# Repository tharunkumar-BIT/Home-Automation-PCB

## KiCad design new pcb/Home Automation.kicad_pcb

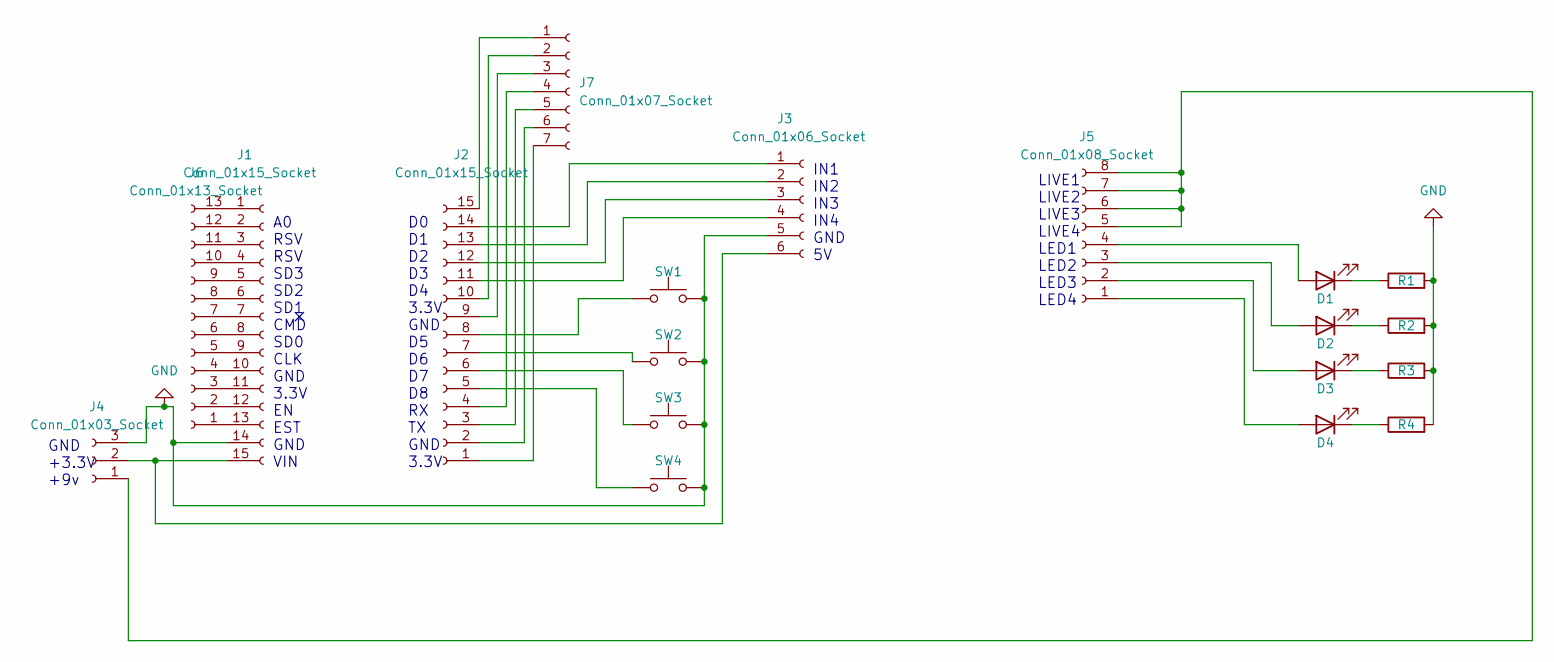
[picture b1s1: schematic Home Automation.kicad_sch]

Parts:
D1, D2, D3, D4: LED; LED_D10.0mm
J1, J2: Conn_01x15_Socket; PinSocket_1x15_P2.54mm_Vertical
J3: Conn_01x06_Socket; PinSocket_1x06_P2.54mm_Vertical
J4: Conn_01x03_Socket; PinSocket_1x03_P2.54mm_Vertical
J5: Conn_01x08_Socket; PinSocket_1x08_P2.54mm_Vertical
J6: Conn_01x13_Socket; PinSocket_1x13_P2.54mm_Vertical
J7: Conn_01x07_Socket; PinSocket_1x07_P2.54mm_Vertical
R1, R2, R3, R4: R; R_Axial_DIN0204_L3.6mm_D1.6mm_P7.62mm_Horizontal
SW1, SW2, SW3, SW4: SW_Push; SW_PUSH_6mm

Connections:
GND: J1.14, J3.5, J4.3, R1.2, R2.2, R3.2, R4.2, SW1.2, SW2.2, SW3.2, SW4.2
unnamed: D1.2 (A), J5.4
unnamed: D1.1 (K), R1.1
unnamed: D2.2 (A), J5.3
unnamed: D2.1 (K), R2.1
unnamed: D3.2 (A), J5.2
unnamed: D3.1 (K), R3.1
unnamed: D4.2 (A), J5.1
unnamed: D4.1 (K), R4.1
unnamed: J1.1, J6.13
unnamed: J1.2, J6.12
unnamed: J1.3, J6.11
unnamed: J1.4, J6.10
unnamed: J1.5, J6.9
unnamed: J1.6, J6.8
unnamed: J1.7, J6.7
unnamed: J1.8, J6.6
unnamed: J1.9, J6.5
unnamed: J1.10, J6.4
unnamed: J1.11, J6.3
unnamed: J1.12, J6.2
unnamed: J1.13, J6.1
unnamed: J1.15, J3.6, J4.2
unnamed: J2.1, J7.7
unnamed: J2.2, J7.6
unnamed: J2.3, J7.5
unnamed: J2.4, J7.4
unnamed: J2.5, SW4.1
unnamed: J2.6, SW3.1
unnamed: J2.7, SW2.1
unnamed: J2.8, SW1.1
unnamed: J2.9, J7.3
unnamed: J2.10, J7.2
unnamed: J2.11, J3.4
unnamed: J2.12, J3.3
unnamed: J2.13, J3.2
unnamed: J2.14, J3.1
unnamed: J2.15, J7.1
unnamed: J4.1, J5.5, J5.6, J5.7, J5.8

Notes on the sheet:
D0 D1 D2 D3 D4 3.3V GND D5 D6 D7 D8 RX TX GND 3.3V
GND +3.3V +9v
IN1 IN2 IN3 IN4 GND 5V
A0 RSV RSV SD3 SD2 SD1 CMD SD0 CLK GND 3.3V EN EST GND VIN
LIVE1 LIVE2 LIVE3 LIVE4 LED1 LED2 LED3 LED4

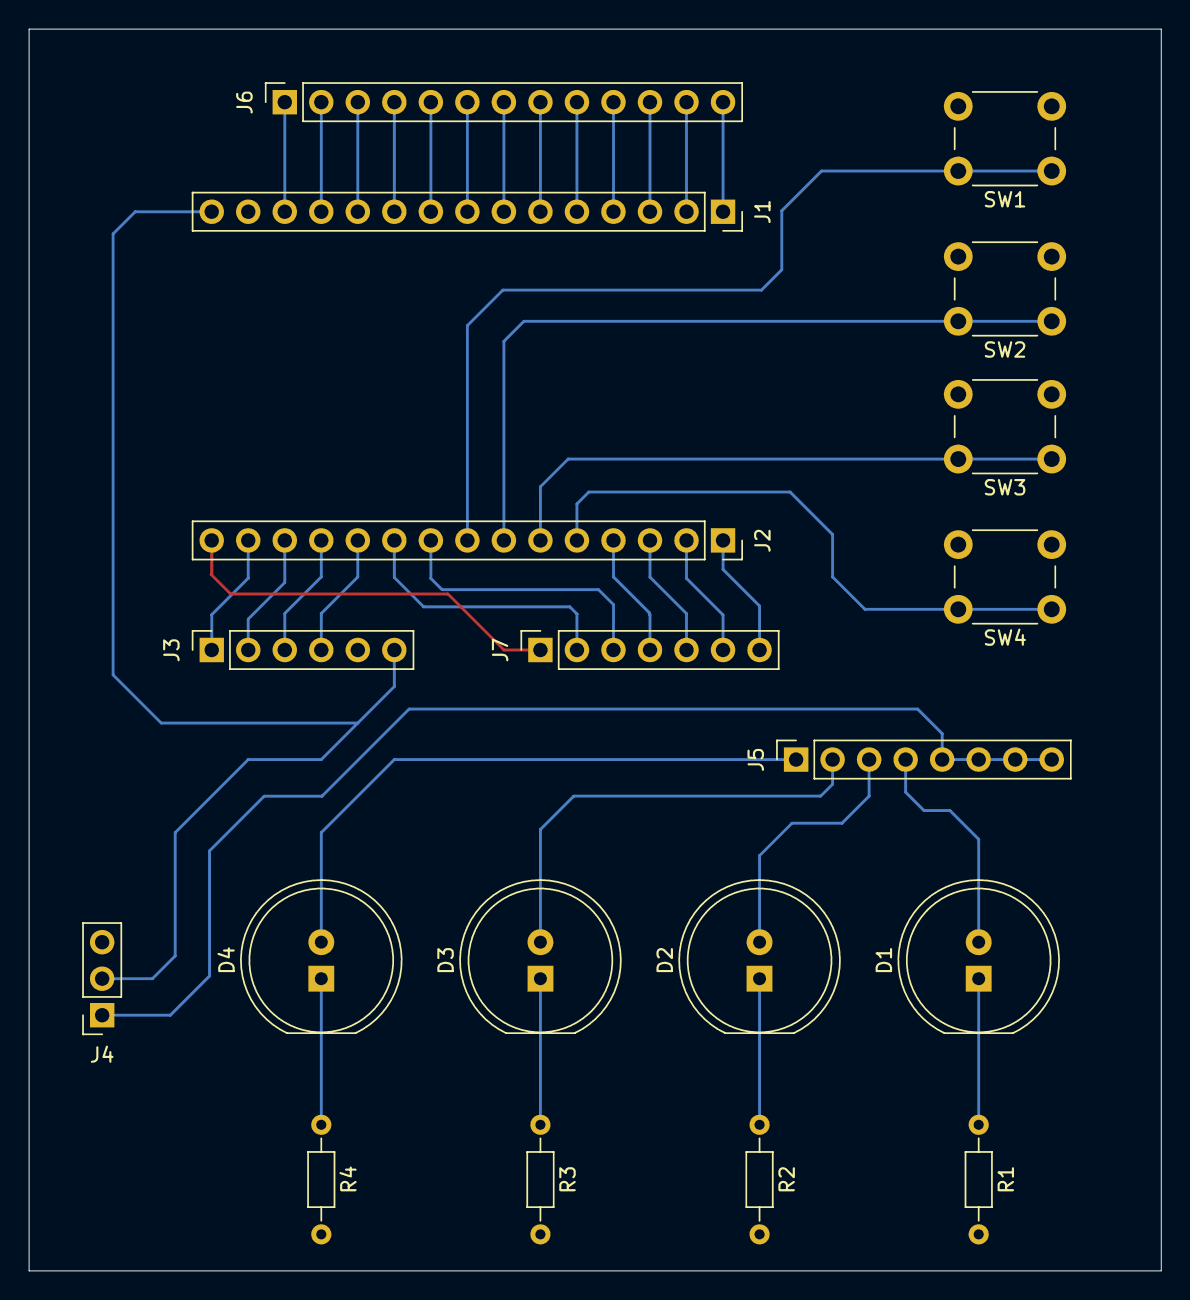
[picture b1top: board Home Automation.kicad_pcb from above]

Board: 2 copper layers, 78.7 x 86.4 mm, 19 parts (0 on the bottom side), 39 nets.

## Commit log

2024-06-27 Gerber files and schematic of Smart Home Automation
